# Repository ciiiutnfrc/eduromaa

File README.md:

# EduRoMAA - Robot Educativo Abierto y de Bajo Costo

El robot móvil EduRoMAA fue desarrollado con fines didácticos para la enseñanza de programación de sistemas embebidos utilizando la EduCIAA (versión educativa de la [Computadora Industrial Abierta Argentina](http://www.proyecto-ciaa.com.ar/)) en el [Centro de Investigación en Informática para la Ingeniería](http://ciii.frc.utn.edu.ar/PublicacionesCIII) de la [Universidad Tecnológica Nacional, Facultad Regional Córdoba](https://www.frc.utn.edu.ar/), bajo el proyecto [Robot móvil de hardware y software abierto con fines educativos en ingeniería electrónica](https://ciii.frc.utn.edu.ar/ciii/proyecto-utn4884/).

El robot EduRoMAA es un robot de tracción diferencial fabricado mediante corte láser e impresión 3D.
Dispone de dos ruedas de tracción controladas de forma independiente a fin de generar la trayectoria deseada, y una semiesfera que hace de apoyo.
Cuenta también con sensores de bajo costo comunes en robótica tales como: paragolpes, tacómetro en las ruedas, sensor de distancia por ultrasonido y sensores infrarrojos para la detección de línea; además de comunicación inalámbrica utilizando el protocolo Bluetooth.
El robot incluye las baterías de alimentación, el cargador por microUSB y fuente de tensión regulada.

El EduRoMAA cuenta con:
  * Tacómetros en las ruedas para la medición de velocidad.
  * Sensor de distancia por ultrasonido en la parte frontal.
  * Sensores de detección de líneas en la parte inferior.
  * Paragolpes en la parte trasera para detección de colisiones.
  * Comunicación inalámbrica por Bluetooth.
  * Bocina o buzzer.
  * Llave de encendido/apagado con LED indicador.
  * Baterías incorporadas con indicador de nivel y cargador por micro-USB.

Para la realización del EduRoMAA se utilizó únicamente software libre: [KiCAD](https://www.kicad.org/) para el circuito electrónico y PCB, [FreeCAD](https://www.freecadweb.org/) para la estructura mecánica y Eclipse IDE con GCC-ARM para el firmware.

## Videos

  * Despiece 3D de los componentes del EduRoMAA: [https://www.youtube.com/watch?v=gHjaK3ePBkI](https://www.youtube.com/watch?v=gHjaK3ePBkI).
  * Prueba de tracción del EduRoMAA: [https://www.youtube.com/watch?v=mks88KmrYdc](https://www.youtube.com/watch?v=mks88KmrYdc).

## Publicaciones
  * Gonzalo Perez-Paina, Martín Baudino, Diego Gonzalez-Dondo, Facundo Navarro, and Patricio Reus Merlo. **"Robot móvil de diseño abierto y bajo costo con fines didácticos basado en la educiaa"**. _In Proceedings of the X Jornadas Argentinas de Robótica (JAR)_. Neuquén, Argentina, 2019.

## Más información
  * [Características principales](doc/Caracteristicas.md).
  * Construcción:
    - Estructura mecánica.
    - Placa de acondicionamiento.
  * Ensamblado.
  * [Conexión con EduCIAA](doc/ConexionEduCIAA.md).
  * [Conexión con BluePill](doc/PlacaAdaptacionBluePill.md).
  * [Códigos de prueba para la versión EduCIAA](codigo/EduCIAA/)
  * [Códigos de prueba para la versión BluePill](codigo/BluePill/)

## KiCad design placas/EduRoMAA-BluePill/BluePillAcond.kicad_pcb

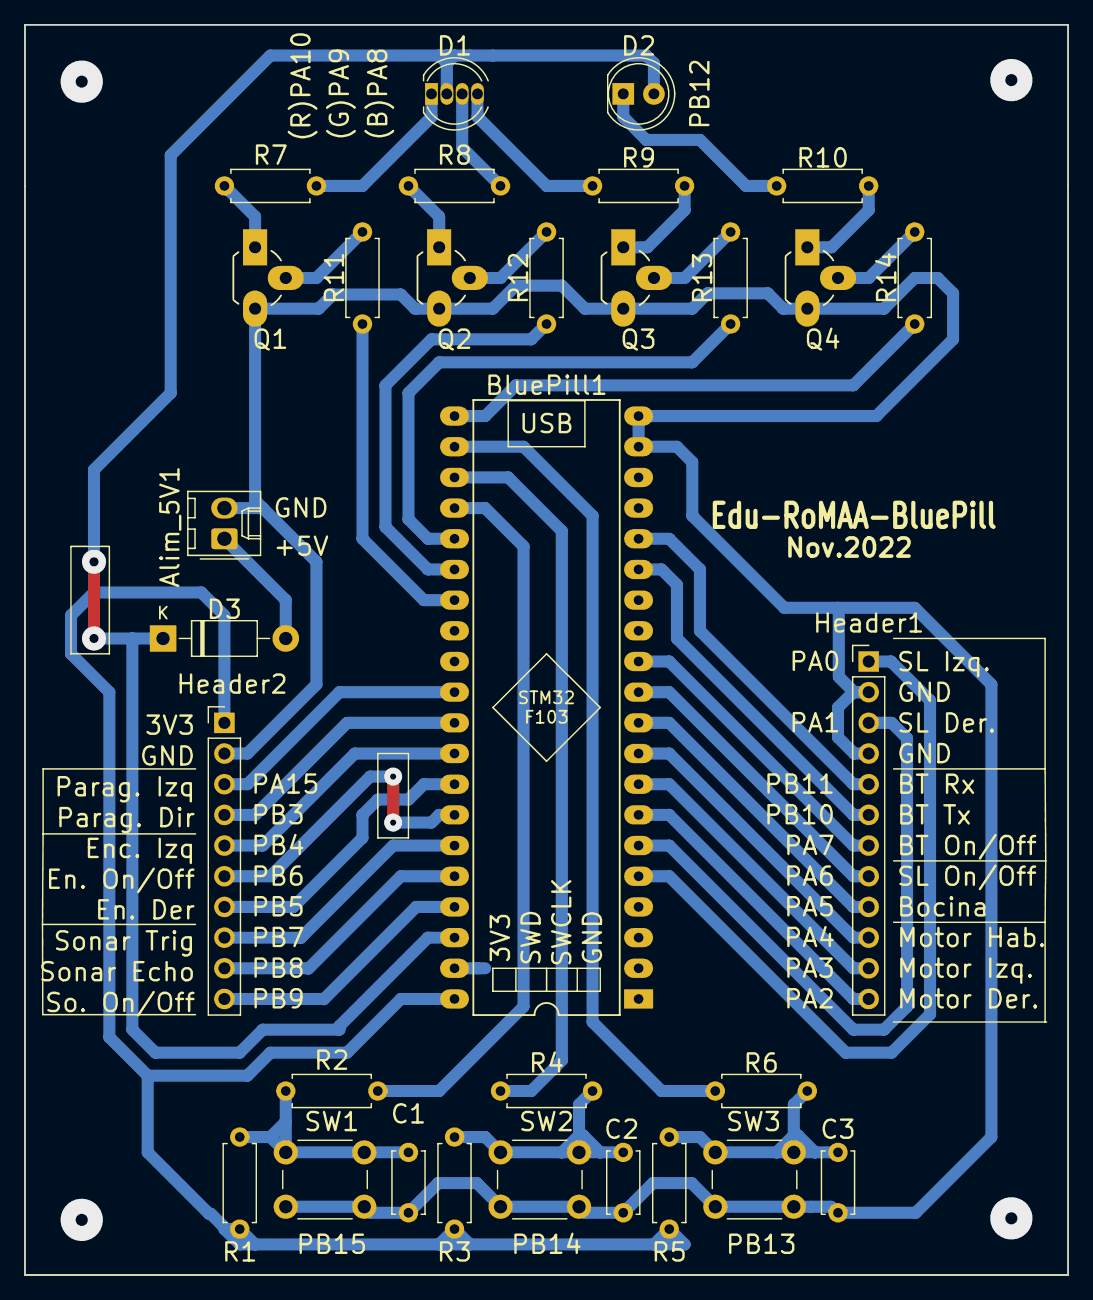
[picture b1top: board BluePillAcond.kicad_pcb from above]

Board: 2 copper layers, 86.4 x 103.5 mm, 31 parts (0 on the bottom side), 44 nets.

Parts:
Alim_5V1: Conn_01x02; Molex_KK-254_AE-6410-02A_1x02_P2.54mm_Vertical
BluePill1: Conn_02x20_Counter_Clockwise; DIP-40_W15.24mm_LongPads
C1, C2, C3: 100nF; C_Disc_D5.0mm_W2.5mm_P5.00mm
D1: LED_RGBA; LED_D5.0mm-4_RGB
D2: LED Rojo; LED_D5.0mm
D3: 1N4007; D_DO-41_SOD81_P10.16mm_Horizontal
Header1: Conn_01x12; PinHeader_1x12_P2.54mm_Vertical
Header2: Conn_01x10; PinHeader_1x10_P2.54mm_Vertical
Q1, Q2, Q3, Q4: BC548; TO-92_Rugged
R1, R3, R5: 10k; R_Axial_DIN0207_L6.3mm_D2.5mm_P7.62mm_Horizontal
R2, R4, R6: 1k; R_Axial_DIN0207_L6.3mm_D2.5mm_P7.62mm_Horizontal
R7, R8, R9, R10: 220; R_Axial_DIN0207_L6.3mm_D2.5mm_P7.62mm_Horizontal
R11, R12, R13, R14: 2k2; R_Axial_DIN0207_L6.3mm_D2.5mm_P7.62mm_Horizontal
SW1, SW2, SW3: SW_Push; SW_PUSH_6mm_H4.3mm

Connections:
5V: BluePill1.38, D1.2, D2.2, D3.1
+3.3VA: BluePill1.40, Header2.1, R1.2, R3.2, R5.2
GND: Alim_5V1.2, BluePill1.19, BluePill1.20, BluePill1.39, C1.2, C2.2, C3.2, Header1.2, Header1.4, Header2.2, Q1.3, Q2.3, Q3.3, Q4.3, SW1.2, SW2.2, SW3.2
unnamed: Alim_5V1.1, D3.2
unnamed: BluePill1.5, Header1.1
unnamed: BluePill1.6, Header1.3
unnamed: BluePill1.7, Header1.12
unnamed: BluePill1.8, Header1.11
unnamed: BluePill1.9, Header1.10
unnamed: BluePill1.10, Header1.9
unnamed: BluePill1.11, Header1.8
unnamed: BluePill1.12, Header1.7
unnamed: BluePill1.15, Header1.6
unnamed: BluePill1.16, Header1.5
unnamed: BluePill1.21, R14.1
unnamed: BluePill1.22, R6.1
unnamed: BluePill1.23, R4.1
unnamed: BluePill1.24, R2.1
unnamed: BluePill1.25, R13.1
unnamed: BluePill1.26, R12.1
unnamed: BluePill1.27, R11.1
unnamed: BluePill1.30, Header2.3
unnamed: BluePill1.31, Header2.4
unnamed: BluePill1.32, Header2.5
unnamed: BluePill1.33, Header2.7
unnamed: BluePill1.34, Header2.6
unnamed: BluePill1.35, Header2.8
unnamed: BluePill1.36, Header2.9
unnamed: BluePill1.37, Header2.10
unnamed: C1.1, R1.1, R2.2, SW1.1
unnamed: C2.1, R3.1, R4.2, SW2.1
unnamed: C3.1, R5.1, R6.2, SW3.1
unnamed: D1.1, R7.1
unnamed: D1.3, R8.1
unnamed: D1.4, R9.1
unnamed: D2.1, R10.1
unnamed: Q1.1, R7.2
unnamed: Q1.2, R11.2
unnamed: Q2.1, R8.2
unnamed: Q2.2, R12.2
unnamed: Q3.1, R9.2
unnamed: Q3.2, R13.2
unnamed: Q4.1, R10.2
unnamed: Q4.2, R14.2

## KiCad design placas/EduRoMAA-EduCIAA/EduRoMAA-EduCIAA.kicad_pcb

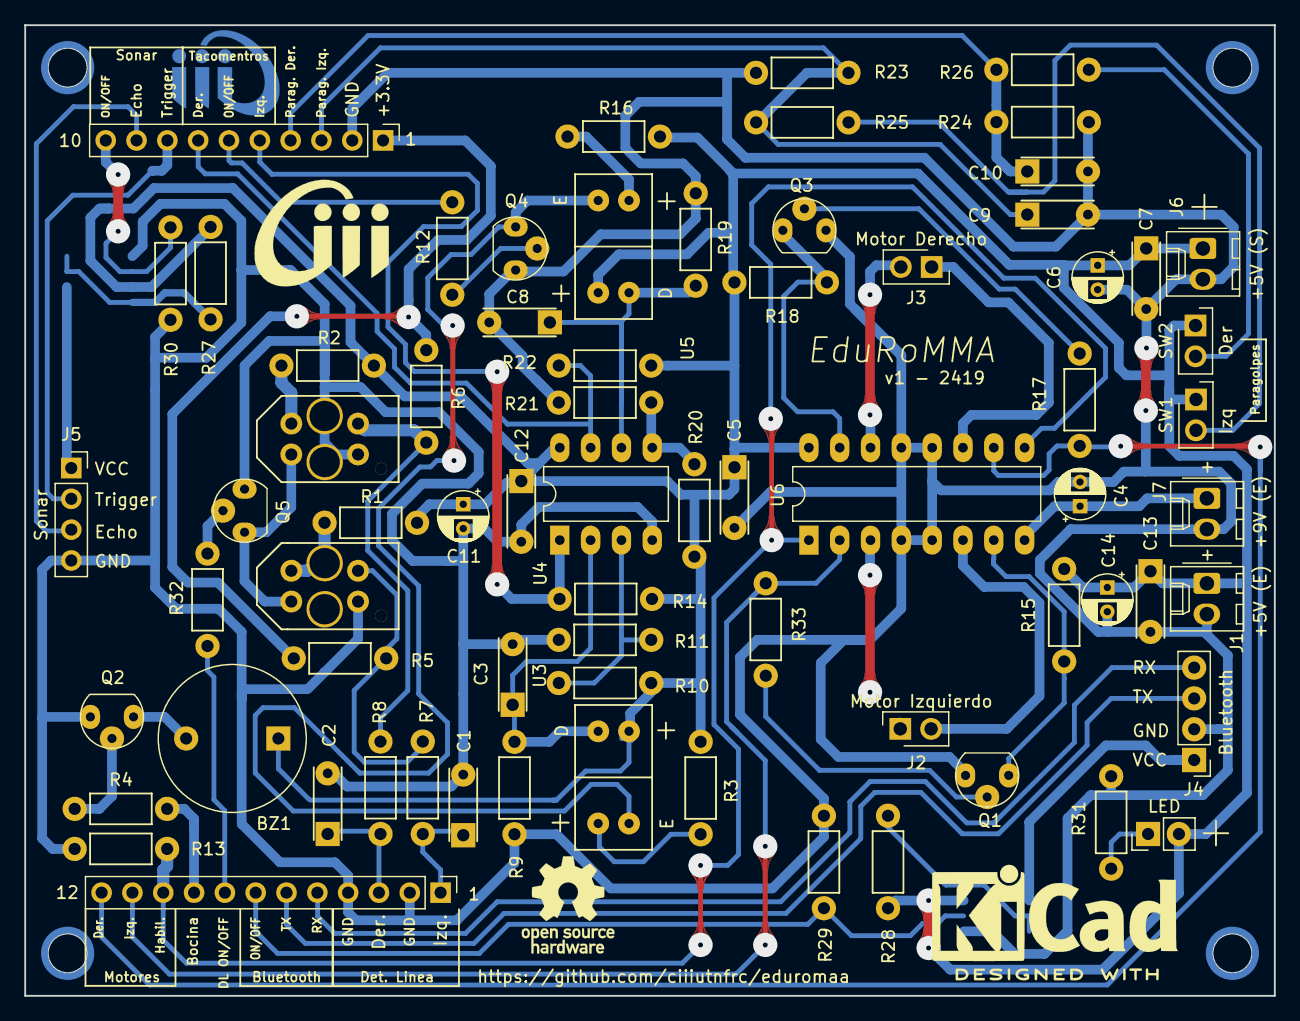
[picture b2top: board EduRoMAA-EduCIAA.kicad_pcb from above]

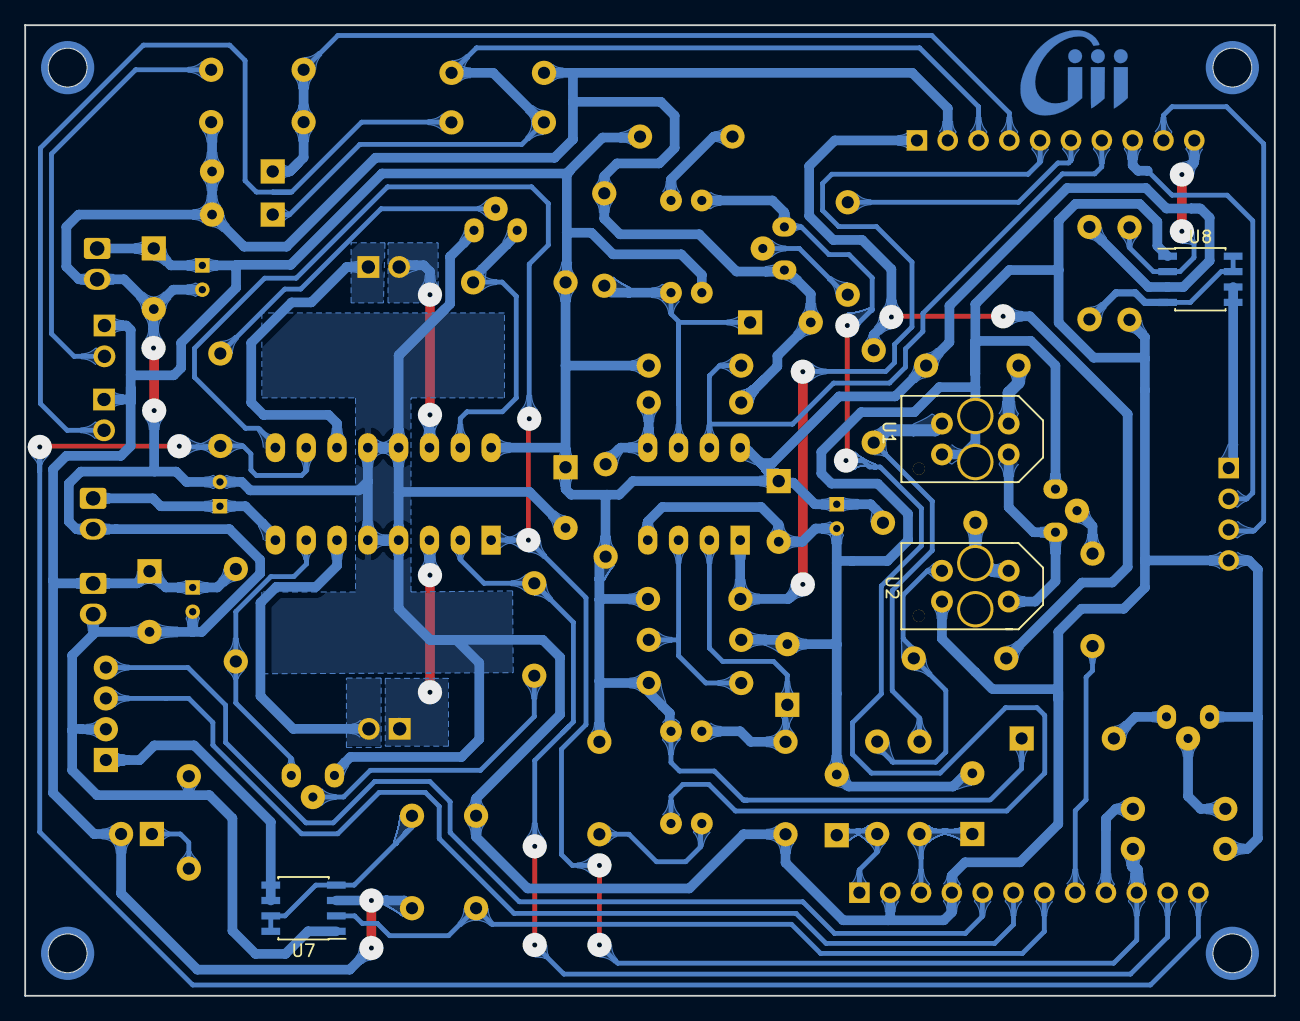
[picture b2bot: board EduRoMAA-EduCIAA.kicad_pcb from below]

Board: 2 copper layers, 103.0 x 80.0 mm, 81 parts (5 on the bottom side), 53 nets.

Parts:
BZ1: Buzzer; Buzzer_12x9.5RM7.6
C1, C2, C3, C5, C7, C8, C9, C10, C12, C13: 0.1u; C_Disc_D6_P5
C4, C6, C11: 10u; CP_Radial_D4.0mm_P2.00mm
C14: 100u; CP_Radial_D4.0mm_P2.00mm
ConDer1: Conn_01x10; PinHeader_1x10_P2.54mm_Vertical
ConIzq1: Conn_01x12; PinHeader_1x12_P2.54mm_Vertical
D1: LED; PinHeader_1x02_P2.54mm_Vertical
J1, J7: DC_IN; Molex_KK-254_AE-6410-02A_1x02_P2.54mm_Vertical
J2: Motor_Izq; HDRV2W64P254_1X2_508X254X864
J3: Motor_Der; HDRV2W64P254_1X2_508X254X864
J4: Bluetooth; PinHeader_1x04_P2.54mm_Vertical
J5: Sonar; PinSocket_1x04_P2.54mm_Vertical
J6: DC_OUT; Molex_KK-254_AE-6410-02A_1x02_P2.54mm_Vertical
Logo_1: Logo_CIII; Logo_CIII_Small
Logo_2: Logo_CIII; Logo_CIII_Small_FSilk
Logo_3: Logo_ohw; OSHW-Logo_7.5x8mm_SilkScreen
Logo_4: Logo_KiCad; KiCad-Logo2_8mm_SilkScreen
MH1, MH2, MH3, MH4: MountingHole; MountingHole_3.2mm_M3_DIN965
Q1, Q2, Q3, Q4, Q5: BC548; TO-92_mod
R1, R2, R3, R16: 220; Resistor_Horizontal_RM7mm
R4, R12, R17, R31, R32, R33: 1k; Resistor_Horizontal_RM7mm
R5, R6: 3.3k; Resistor_Horizontal_RM7mm
R7, R8, R23, R24: 22k; Resistor_Horizontal_RM7mm
R9, R10, R11, R13, R14, R15, R18, R19, R20, R21, R22, R25, R26, R27, R28, R29, R30: 10k; Resistor_Horizontal_RM7mm
SW1, SW2: SW_Push; HDRV2W64P254_1X2_508X254X864
U1, U2: TCRT5000
U3, U5: TCST1103
U4: LM393; DIP-8_W7.62mm_LongPads
U6: L293D; DIP-16_W7.62mm_LongPads
U7, U8: IRF7105; SOIC-8_3.9x4.9mm_P1.27mm

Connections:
+3V3: ConDer1.1, R5.1, R6.1
+5V: BZ1.1, C5.1, C6.1, C7.1, C11.1, C12.1, C13.1, C14.1, D1.2, J1.1, J6.1, R1.1, R2.1, R3.1, R10.1, R14.1, R15.1, R16.1, R18.1, R20.1, R22.1, R27.1, R28.1, SW1.1, SW2.1, U3.3, U4.8, U5.3, U6.16, U7.3, U8.3
+9V: C4.1, J7.1, U6.8
/C_1: Q1.1, R15.2, U6.7
/C_2: Q3.1, R18.2, U6.15
/Motor_Der1: J3.1, U6.11
/Motor_Der2: J3.2, U6.14
/Motor_Izq1: J2.1, U6.3
/Motor_Izq2: J2.2, U6.6
/Vcc_BT: J4.1, U7.5, U7.6
/Vcc_Sonar: J5.1, U8.5, U8.6
Bluetooth_OnOff: ConIzq1.7, R29.1, U7.2
Bluetooth_Rx: ConIzq1.5, J4.4
Bluetooth_Tx: ConIzq1.6, J4.3
Bumper_Der: C10.1, ConDer1.4, R24.1, R26.1
Bumper_Izq: C9.1, ConDer1.3, R23.2, R25.1
Buzzer: ConIzq1.9, R4.2
ENABLE_Motors: ConIzq1.10, R13.1, U6.1, U6.9
Encoder_Der: ConDer1.7, R22.2, U4.7
Encoder_Izq: ConDer1.5, R14.2, U4.1
Encoder_OnOff: ConDer1.6, R12.2
GND: C1.2, C2.2, C3.2, C4.2, C5.2, C6.2, C7.2, C8.2, C9.2, C10.2, C11.2, C12.2, C13.2, C14.2, ConDer1.2, ConIzq1.2, ConIzq1.4, J1.2, J4.2, J5.4, J6.2, J7.2, Q1.3, Q2.3, Q3.3, Q4.3, Q5.3, R9.2, R11.2, R13.2, R19.2, R21.2, R23.1, R24.2, R29.2, R30.2, R31.1, U1.4, U2.4, U4.4, U6.4, U6.5, U6.12, U6.13, U7.1, U8.1
GND_IRLED1: Q5.1, U1.2, U2.2
GND_LED2: Q4.1, U3.2, U5.2
unnamed: BZ1.2, Q2.1
unnamed: C3.1, R9.1, U3.4, U4.2
unnamed: C8.1, R19.1, U4.6, U5.4
unnamed: D1.1, R31.2
unnamed: Q1.2, R33.1
unnamed: Q2.2, R4.1
unnamed: Q3.2, R17.1
unnamed: Q4.2, R12.1
unnamed: Q5.2, R32.1
unnamed: R1.2, U2.1
unnamed: R2.2, U1.1
unnamed: R3.2, U3.1
unnamed: R5.2, R7.2, U2.3
unnamed: R6.2, R8.2, U1.3
unnamed: R10.2, R11.1, U4.3
unnamed: R16.2, U5.1
unnamed: R20.2, R21.1, U4.5
unnamed: R25.2, SW1.2
unnamed: R26.2, SW2.2
unnamed: R27.2, U8.4, U8.7, U8.8
unnamed: R28.2, U7.4, U7.7, U7.8
PWM_Der: ConIzq1.12, R17.2, U6.10
PWM_Izq: ConIzq1.11, R33.2, U6.2
SegLinea_Der: C2.1, ConIzq1.3, R8.1
SegLinea_Izq: C1.1, ConIzq1.1, R7.1
SegLinea_OnOff: ConIzq1.8, R32.2
Sonar_Echo: ConDer1.9, J5.3
Sonar_OnOff: ConDer1.10, R30.1, U8.2
Sonar_Trig: ConDer1.8, J5.2

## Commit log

2019-04-26 Agregado archivos de CAD 3D
2019-04-27 Editados archivos README
2019-04-29 Editado archivo FreeCAD de las tapas del robot
    Eliminado un hueco de sujeción con tornillos, queda uno solo.
    Agregado archivo .gitignore para ignorar archivos backups de FreeCAD.
2019-05-04 Editado diseño CAD de las tapas superior e inferior
    Corregido error de cotas de referencia de la tapa superior.
2019-05-04 Perforaciones de tapa superior
    Agregada perforaciones para sujetar la placa EduCIAA a la tapa superior
2019-05-04 Editado CAD de la tapa inferior
    Agregado perforaciones para los tornillos de sujeción de la placa de
    acondicionamiento a la tapa inferior
2019-05-06 Modificado diseño 3D de la tapa inferior
    Modificado para coincidir con las dimensiones del PCB.
2019-05-06 Modificado diseño 3D de tapa superior
    Modificada ranura pasacables y huecos para los tornillos de la EduCIAA
    de la tapa superior.
2019-05-06 Corregido error de encastres en tapa superior
2019-05-07 Firmware EduROMAA: primera versión funcional
    Archivo Readme.md contiene todas las definiciones del pinout de la placa
    EduCIAA para conexión con EduRoMAA.
    * Módulo Paragolpes:
    * En "paragolpes.h" se encuentran 2 implementaciones:
    * Utilizando solo GPIO para leer el estado de cada paragolpes
    * Utilizando interrupciones externas
2019-05-11 Corregido error de guardabarros
    Corregido error de 5mm en los guardabarros, se corrieron los laterales
    hacia adentro.
2019-05-11 Archivos para generar el dibujo para el PCB
    Agregados archivos que permiten generar el dibuo (en formato dxf) de
    ayuda para ubicar los componentes de la placa (PCB).
2019-05-16 Corregido error del diseño CAD de los laterales
    Corregido error en el diseño CAD de los encastres de los motores en los
    laterales del robot.
2019-05-20 Agregado archivo de ensamble de la estructura
    Agregado archivo de ensamble de la estructura del robot, el cual incluye
    las tapas inferior y superior, los laterales, la tapa delantera y
    trasera.
2019-05-20 Agregado archivos para el corte láser (svg y pdf)
    Modificado los archivos de diseño para agregar proyección 2D para
    exportar a svg.
    Creado archivos svg para corte láser y pdf con todas las piezas.
2019-05-20 Modificado archivo de ensample de estructura
    Actualizada tapa inferior con versión con perforaciones de la placa de
    acondicionamiento.
2019-05-21 Cambio de nombre de carpeta Firmware por 'código'
2019-05-21 Actualizado README.md del directorio cad3d
2019-05-21 Agregado diseño de pieza de apoyo
    Agregado diseño de pieza de apoyo que hace de reemplazo de una rueda
    castor.
    Agregado transparencia a las piezas del ensamble.
2019-05-24 Limpieza de estructura de directorios
2019-05-24 Nueva carpeta codigo con todos los archivos del proyecto
2019-05-30 Modificada diseño CAD 3D de la tapa superior
    Tapa superior modificada para incluir las perforaciones para la carga de
    la baterías. Modificados también los archivos de corte (.svg)
2019-05-30 Modificado archivo README.md de la raíz
    Agregado enlace a video de YouTube en README raíz.
2019-05-31 Modificando el gitignore para KiCAD
2019-05-31 [placas] Agregando la placa EduRoMAA-EduCIAA al proyecto
2019-06-03 Módulo Bluetooth y mejoras varias
    * Agregado módulo Bluetooth y programado prueba de uso. La prueba
    devuelve por el puerto USB lo recibido por BT.
    * Mofificado iniMotores para que devuelva "void" ya que no tiene
    condición de bloqueo.
    * Modificado código de prueba de motores para que genere rampas de
    velocidad en avance y en retroceso.
2019-06-03 Actualizado README.md principal
    Agregada información sobre el EduRomAA
2019-06-03 Reorganizo esquematico y uno librerias
    Reorganización general, elimino net repetidas y uno las librerias en una sola
2019-06-05 Integración de Módulos
    - Los archivos eduromaa.h y .c se encuentran agregados contienen
    funciones de inicialización del EduRoMAA como robot, y no como partes
    aisladas.
    - Modificado a ascendente el flanco de generación de interrupción de los
    paragolpes, ya que si no la señal se genera cuando el robot rebota, y no
    evita la colisión.
2019-06-07 Agrego carpeta para exportar pdf's
    Se creo una carpeta destinada para archivos de fabricacion, tanto de la
    placa como la parte mecánica.
2019-06-10 Migración a plantilla cese-edu-ciaa-template r1.1
    * Modificación de TODOS los proyectos de prueba para compilar con
    configuración de Makefiles de la plantilla
    * Agregado a .gitignore los directorios de salida por proyecto
    * Agregados ejemplos de Make
2019-06-10 [PCB] Modifico serigrafia y re-ruteo.
    Modifico serigrafia y algo de ruteo
2019-06-10 Adaptaciones de código de comunicación y PWM
    * Modificación frecuencia de PWM en sapi_pwm.c para eliminar el ruido
    molesto que producen los motores, especialmente cuando el robot está
    parado. Este valor está hardcodeado en SAPI.
    * Cambio de funciones de impresió, de uartWriteString a printf.
    Simplifica el código de usuario y evita el uso de "itoa".
    * Cambio de tasa de transferencia de UART_USB de 9600 a 115200. Elimina
2019-06-11 [PCB] Revisiones de ruteado.
2019-06-13 [PCB] Agrego serigrafia complementaria
    Agrego símbolos para serigrafia, lista para revision
2019-06-13 [PCB] Arreglo teardrops
2019-06-13 [PCB] Minimas modificaciones al ruteo, falta hacer un DRC
2019-06-14 [PCB] Agrego nombre de placa y reorganizo pistas.
2019-06-14 Actualizado README principal
    Agregado link a video de youtube. Borrados archivos basura.
2019-06-15 Borrado archivos basura
2019-06-15 Renombrado de directorios
2019-06-18 Agrego BOM, PDF y modifico esquematico
    Se modifica las resistencias R5,R6 a 3,3kohm. Se modifica fp
    de uno de los TCRT5000, agrego pdf de serigrafia frontal,
    pistas inferiores y archivos para fabricacion.
    Agrego BOM, interactivo y html.
2019-06-19 Actualizo footprints y modifico pdf de fabricacion
    Se dibujo la capa de fabricacion en el footprints de los componentes,
    se agrego contorno, puentes, en capa de fabricacion, exporto todo en
    pdf Ffab.
2019-06-19 Elimino basura, actualizo ibom
2019-07-09 Ejemplo de uso del puerto serie con printf
2019-07-15 Ejemplos para el curso
2019-07-15 Bugfixes tacómetros
2019-07-16 Aplicación con Bluetooth
2020-04-18 Modifica los archivos de cabecera de la biblioteca
    - Cambia los header guards
    - Acomoda las tabulaciones
2020-04-18 Refactorización de la biblioteca
    - Ajusta tamaño de las tabulaciones
    - Pone comentarios al estilo de C (/* */)
2020-04-18 Modifica orden de parámetros en función de motores
    Se invierte el orden de los parámetros en una función que actúa sobre
    ambos motores para que todas las funciones similares tengan los
    parámetros en el mismo orden.
2021-07-31 Agrega documentación en README principal
2021-07-31 Actualiza doc. sobre características del robot
2021-10-20 Agrega documentación md y actualiza README
2023-03-17 [EduRoMAA-BluePill] Agrega archivos kicad Agrega los archivos kicad del pcb de la placa de adaptacion
2023-03-17 Agrega ignores para kicad6
2023-04-19 Agrega .md de placa adaptación con la bluepill Agrega .md de la placa de adaptación para la bluepill.
2023-04-26 Mueve archivos de codigos de la educiaa Mueve códigos de prueba del EduRoMAA versión EduCIAA a una carpeta EduCIAA
2023-04-26 Agrega codigos arduino de testeo para la bluepill Agrega códigos para probar los perifericos del EduRoMAA de la versión BluePill
2023-04-26 Agrega los links a códigos segun placa en README Agrega los links a códigos de prueba segun placa Educiaa o bluepill
